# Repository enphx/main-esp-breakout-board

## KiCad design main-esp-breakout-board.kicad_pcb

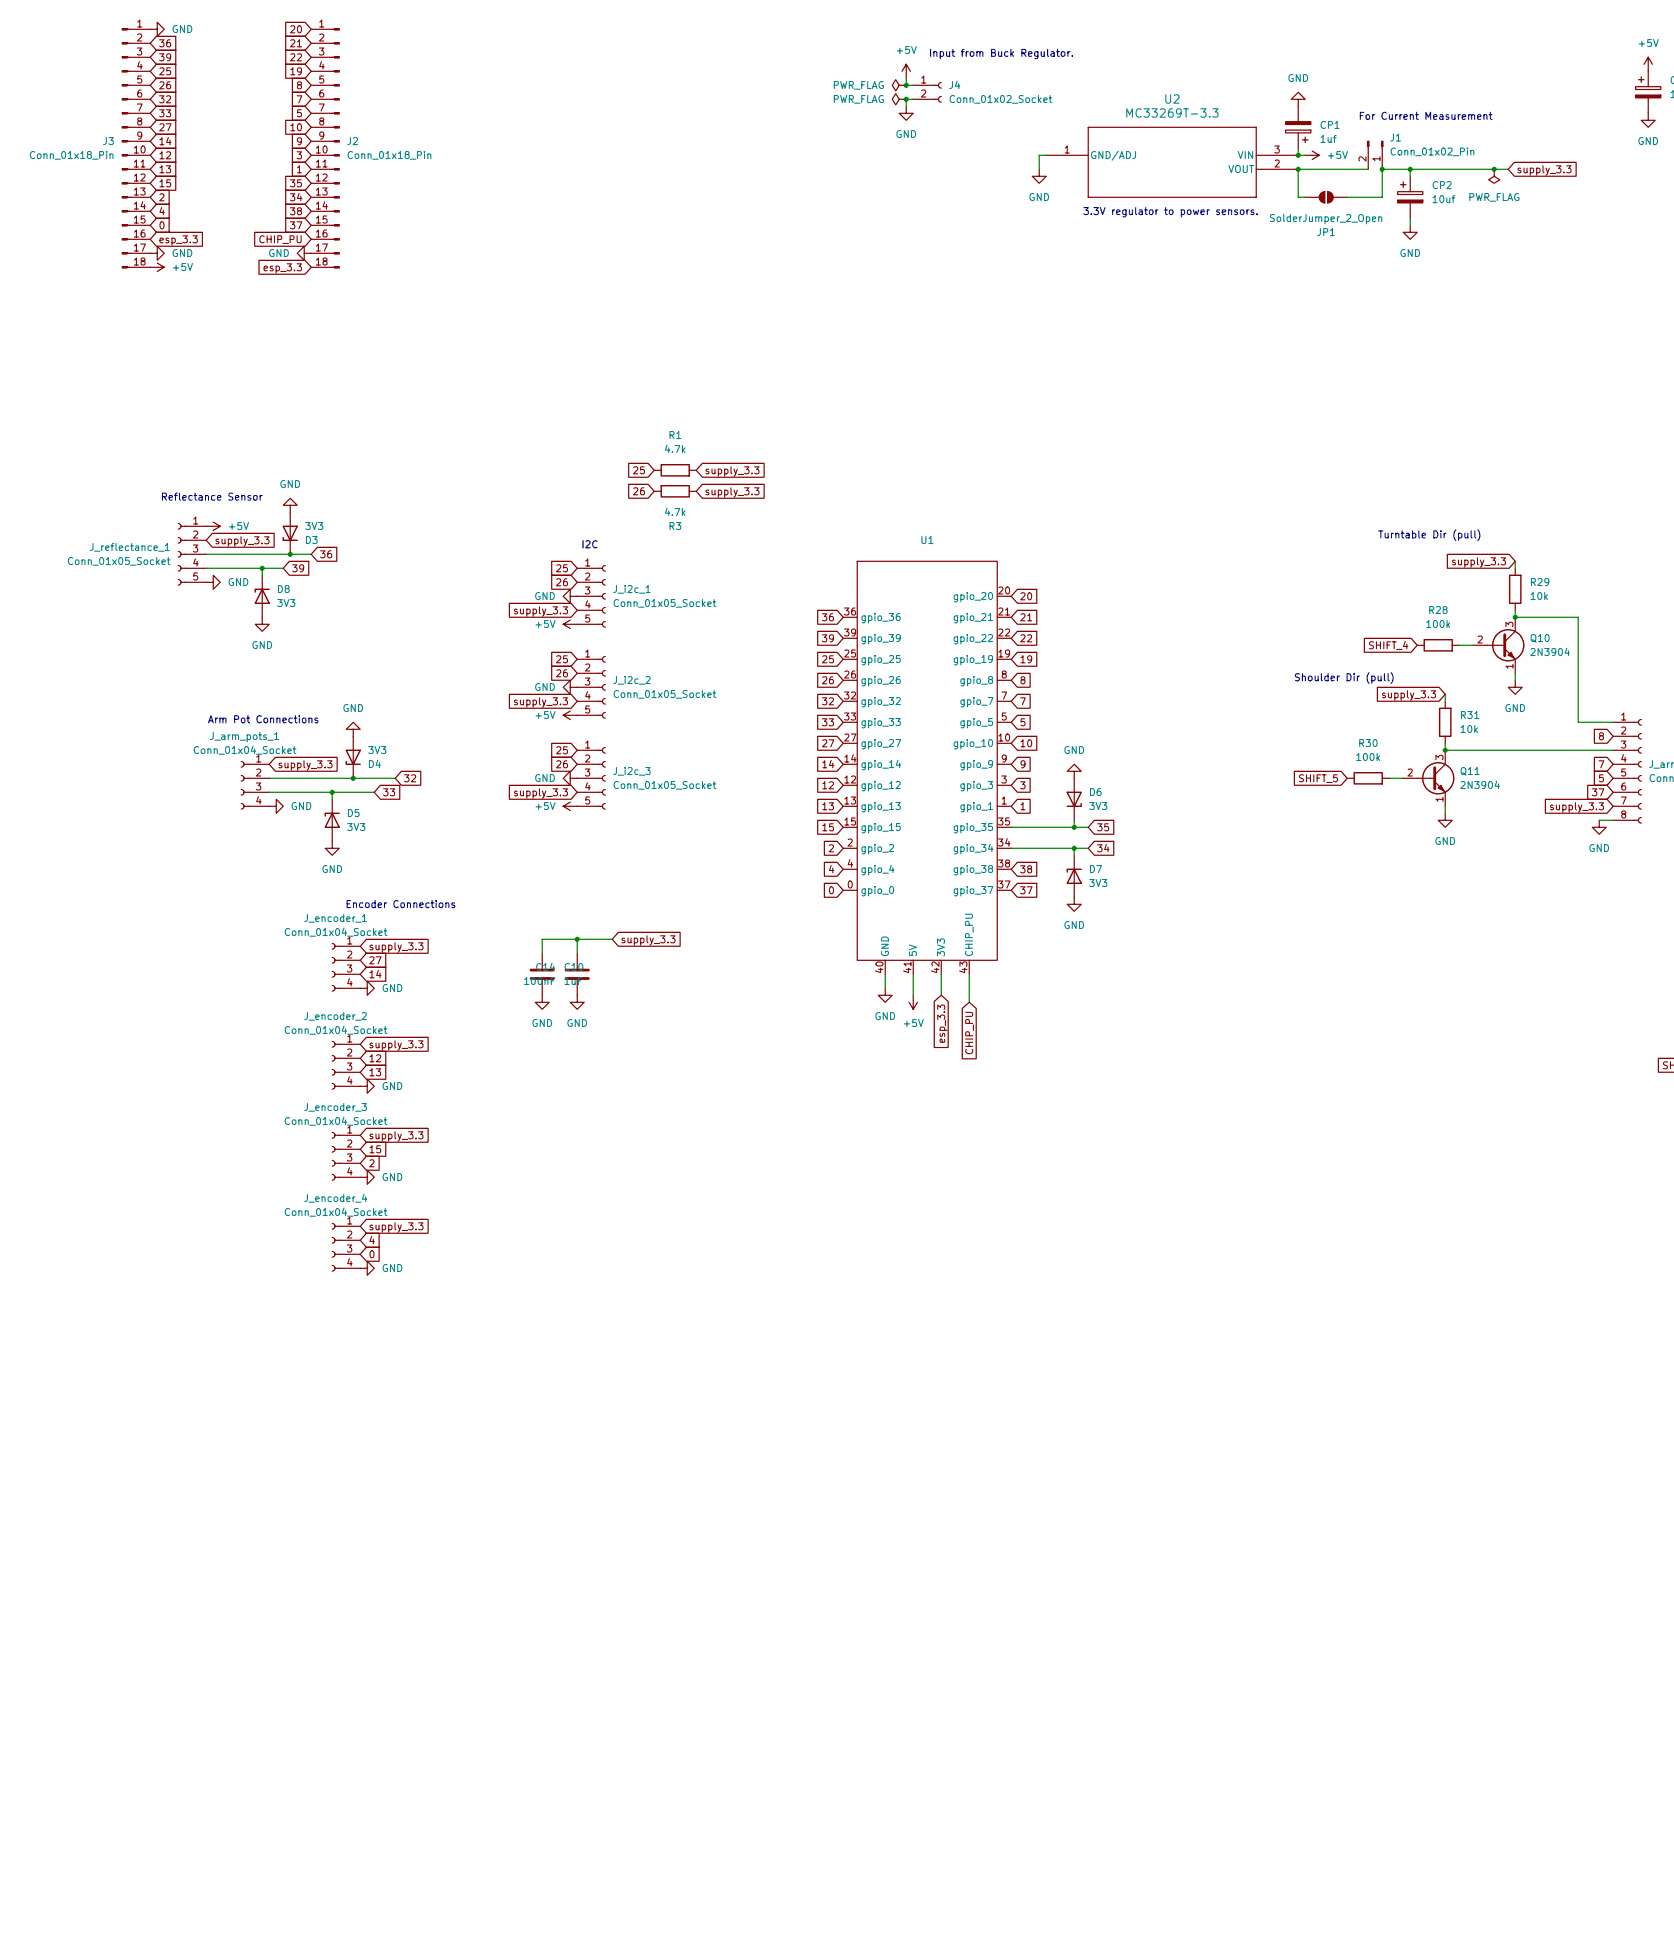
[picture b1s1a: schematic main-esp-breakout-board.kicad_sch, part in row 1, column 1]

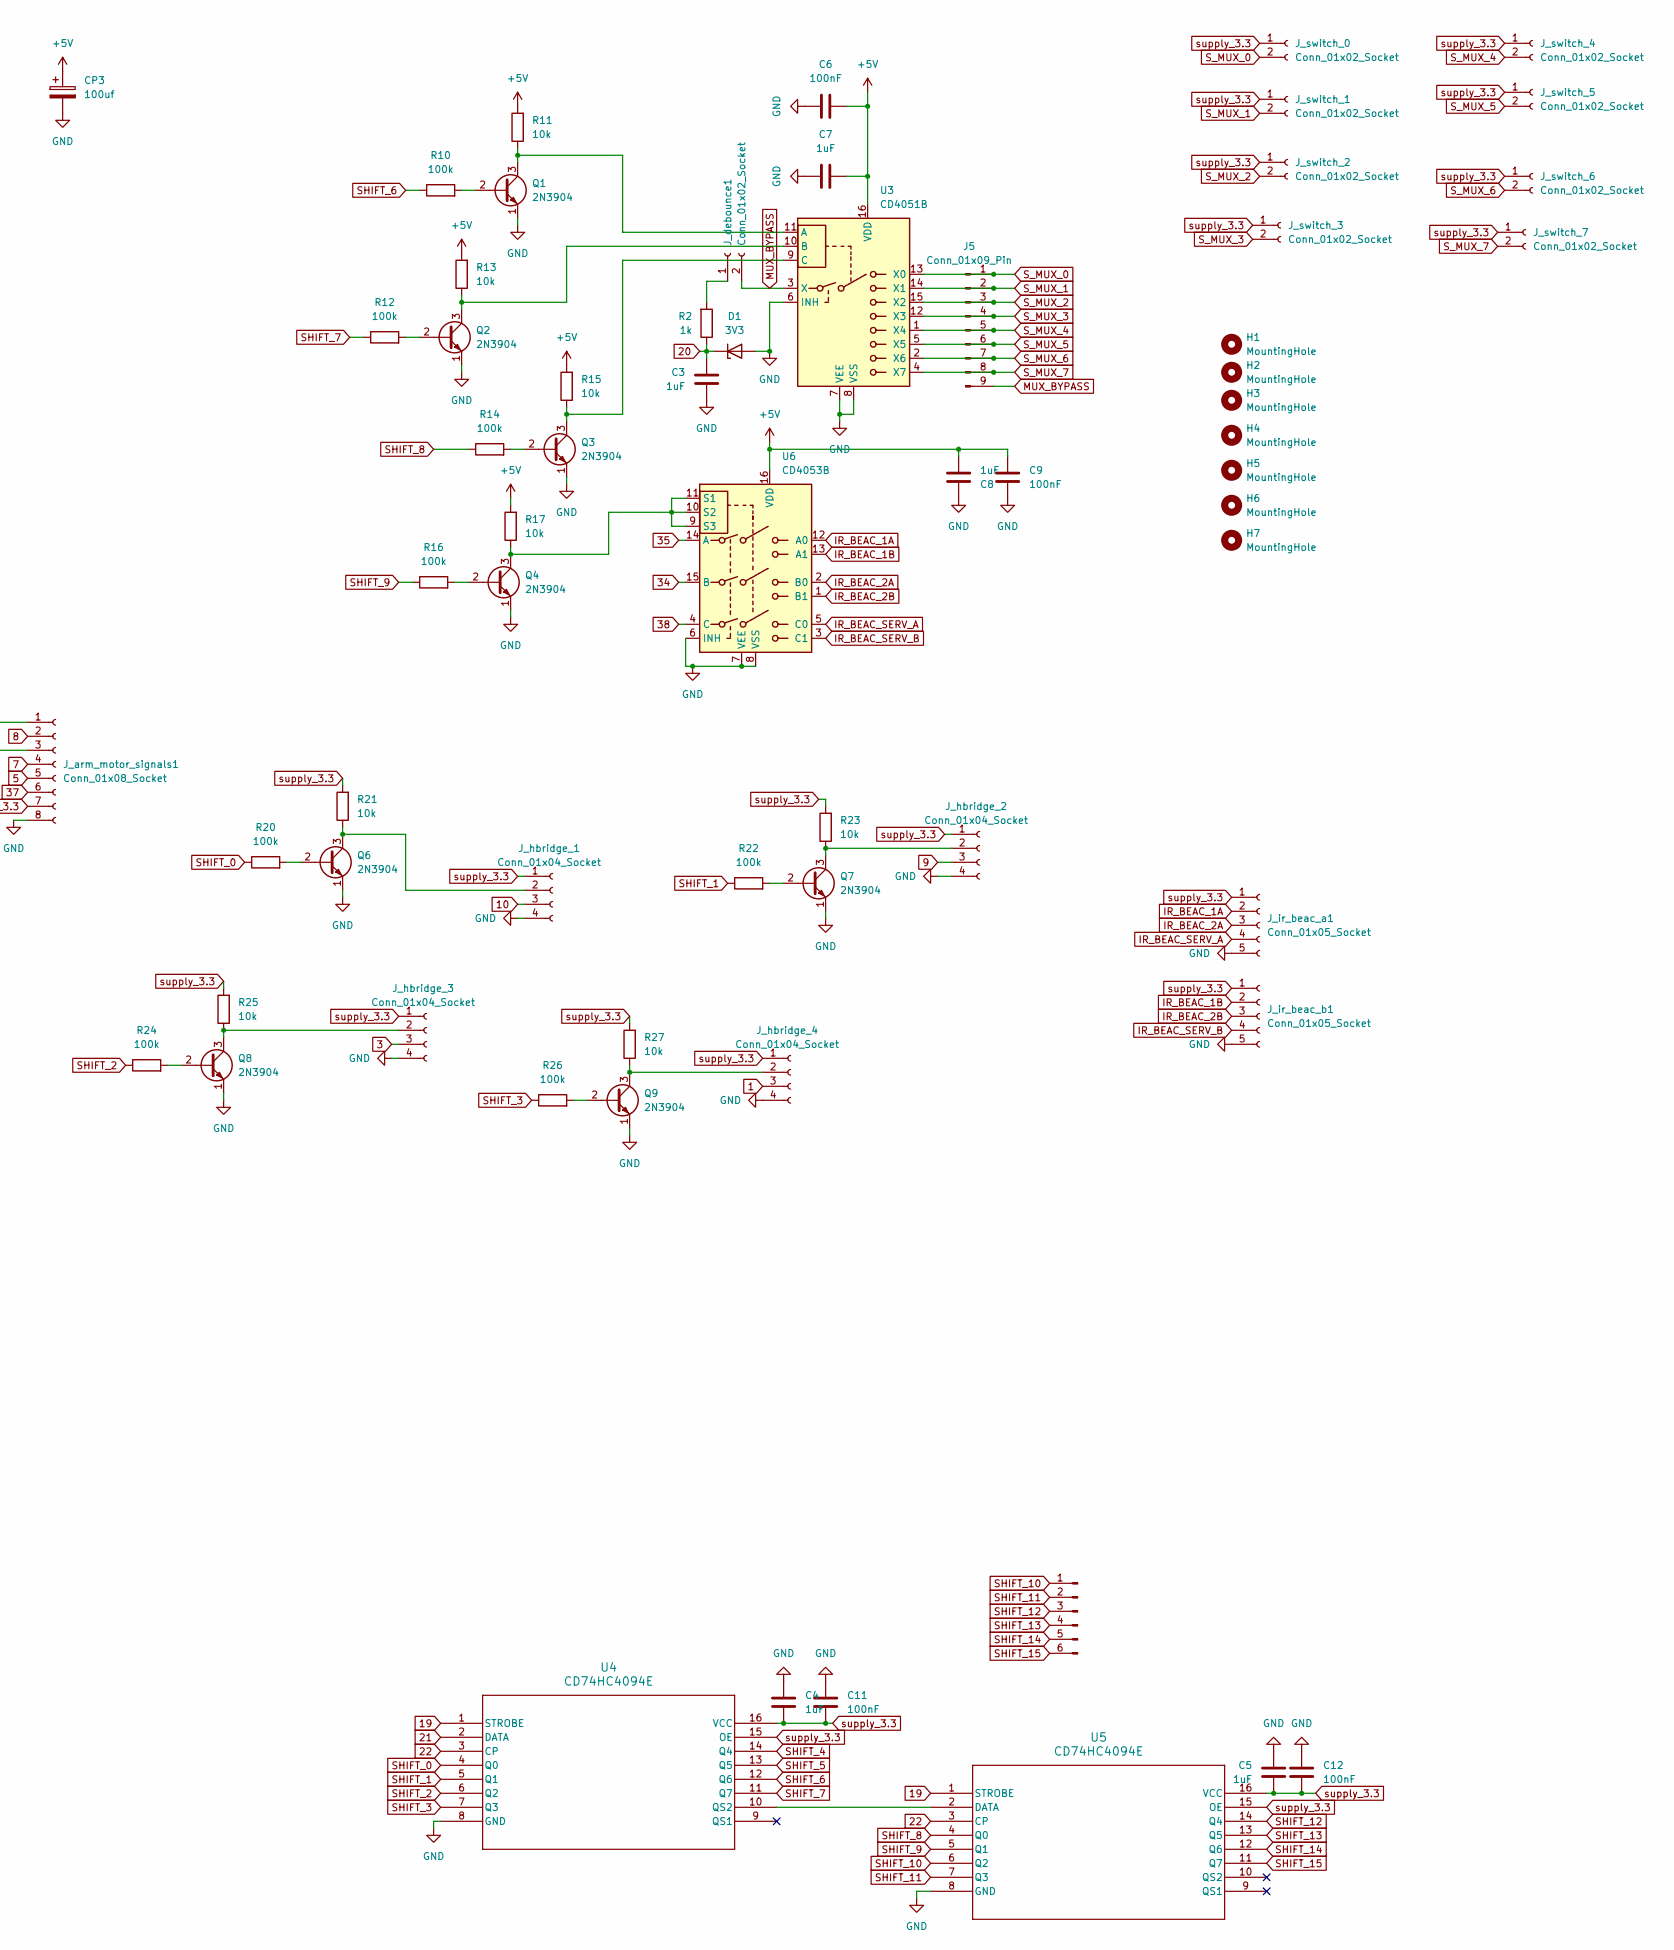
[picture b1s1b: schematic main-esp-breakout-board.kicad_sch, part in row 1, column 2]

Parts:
C3, C4, C5, C7, C8, C10: 1uF; Capacitor_With_Value_uF_small
C6, C9, C11, C12, C14: 100nF; Capacitor_With_Value_nF
CP1: 1uf; Capacitor_With_Value_uF_small
CP2: 10uf; Capacitor_With_Value_uF_small
CP3: 100uf; Capacitor_With_Value_uF_big
D1, D3, D4, D5, D6, D7, D8: 3V3; zener_diode
H1, H2, H3, H4, H5, H6, H7: MountingHole; MountingHole_3.2mm_M3
J1: Conn_01x02_Pin; PinHeader_1x02_P2.54mm_Vertical
J2, J3: Conn_01x18_Pin; PinHeader_1x18_P2.54mm_Vertical
J4: Conn_01x02_Socket; Power_Connector
J5: Conn_01x09_Pin; PinHeader_1x09_P2.54mm_Vertical
JP1: SolderJumper_2_Open; SolderJumper-2_P1.3mm_Open_RoundedPad1.0x1.5mm
J_arm_motor_signals1: Conn_01x08_Socket; JST_XH_B8B-XH-A_1x08_P2.50mm_Vertical
J_arm_pots_1: Conn_01x04_Socket; JST_XH_B4B-XH-A_1x04_P2.50mm_Vertical
J_debounce1: Conn_01x02_Socket; JST_XH_B2B-XH-A_1x02_P2.50mm_Vertical
J_encoder_1, J_encoder_2, J_encoder_3, J_encoder_4: Conn_01x04_Socket; JST_XH_B4B-XH-A_1x04_P2.50mm_Vertical
J_hbridge_1, J_hbridge_2, J_hbridge_3, J_hbridge_4: Conn_01x04_Socket; JST_XH_B4B-XH-A_1x04_P2.50mm_Vertical
J_i2c_1, J_i2c_2, J_i2c_3: Conn_01x05_Socket; JST_XH_B5B-XH-A_1x05_P2.50mm_Vertical
J_ir_beac_a1: Conn_01x05_Socket; JST_XH_B5B-XH-A_1x05_P2.50mm_Vertical
J_ir_beac_b1: Conn_01x05_Socket; JST_XH_B5B-XH-A_1x05_P2.50mm_Vertical
J_reflectance_1: Conn_01x05_Socket; JST_XH_B5B-XH-A_1x05_P2.50mm_Vertical
J_shift_register_extra1: Conn_01x06_Pin; PinSocket_1x06_P2.54mm_Vertical
J_switch_0, J_switch_1, J_switch_2, J_switch_3, J_switch_4, J_switch_5, J_switch_6, J_switch_7: Conn_01x02_Socket; JST_XH_B2B-XH-A_1x02_P2.50mm_Vertical
Q1, Q2, Q3, Q4, Q6, Q7, Q8, Q9, Q10, Q11: 2N3904; TO-92_Inline
R1, R3: 4.7k; Resistor_With_Value
R2: 1k; Resistor_With_Value
R10, R12, R14, R16, R20, R22, R24, R26, R28, R30: 100k; Resistor_With_Value
R11, R13, R15, R17, R21, R23, R25, R27, R29, R31: 10k; Resistor_With_Value
U1: ESP32_Pico_Devkit
U2: MC33269T-3.3; TO220-3_ONS
U3: CD4051B; N16
U4, U5: CD74HC4094E; N16
U6: CD4053B; N16

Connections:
0: J3.15, J_encoder_4.3, U1.0 (gpio_0)
1: J2.11, J_hbridge_4.3, U1.1 (gpio_1)
2: J3.13, J_encoder_3.3, U1.2 (gpio_2)
3: J2.10, J_hbridge_3.3, U1.3 (gpio_3)
4: J3.14, J_encoder_4.2, U1.4 (gpio_4)
5: J2.7, J_arm_motor_signals1.5, U1.5 (gpio_5)
7: J2.6, J_arm_motor_signals1.4, U1.7 (gpio_7)
8: J2.5, J_arm_motor_signals1.2, U1.8 (gpio_8)
9: J2.9, J_hbridge_2.3, U1.9 (gpio_9)
10: J2.8, J_hbridge_1.3, U1.10 (gpio_10)
12: J3.10, J_encoder_2.2, U1.12 (gpio_12)
13: J3.11, J_encoder_2.3, U1.13 (gpio_13)
14: J3.9, J_encoder_1.3, U1.14 (gpio_14)
15: J3.12, J_encoder_3.2, U1.15 (gpio_15)
19: J2.4, U1.19 (gpio_19), U4.1 (STROBE), U5.1 (STROBE)
20: C3.1, D1.1 (K), J2.1, R2.1, U1.20 (gpio_20)
21: J2.2, U1.21 (gpio_21), U4.2 (DATA)
22: J2.3, U1.22 (gpio_22), U4.3 (CP), U5.3 (CP)
25: J3.4, J_i2c_1.1, J_i2c_2.1, J_i2c_3.1, R1.1, U1.25 (gpio_25)
26: J3.5, J_i2c_1.2, J_i2c_2.2, J_i2c_3.2, R3.2, U1.26 (gpio_26)
27: J3.8, J_encoder_1.2, U1.27 (gpio_27)
32: D4.1 (K), J3.6, J_arm_pots_1.2, U1.32 (gpio_32)
33: D5.1 (K), J3.7, J_arm_pots_1.3, U1.33 (gpio_33)
34: D7.1 (K), J2.13, U1.34 (gpio_34), U6.15 (B)
35: D6.1 (K), J2.12, U1.35 (gpio_35), U6.14 (A)
36: D3.1 (K), J3.2, J_reflectance_1.3, U1.36 (gpio_36)
37: J2.15, J_arm_motor_signals1.6, U1.37 (gpio_37)
38: J2.14, U1.38 (gpio_38), U6.4 (C)
39: D8.1 (K), J3.3, J_reflectance_1.4, U1.39 (gpio_39)
+5V: C6.2, C7.1, C8.1, C9.2, CP1.1, CP3.1, J3.18, J4.1, J_i2c_1.5, J_i2c_2.5, J_i2c_3.5, J_reflectance_1.1, R11.2, R13.2, R15.2, R17.2, U1.41 (5V), U2.3 (VIN), U3.16 (VDD), U6.16 (VDD)
CHIP_PU: J2.16, U1.43 (CHIP_PU)
GND: C3.2, C4.2, C5.2, C6.1, C7.2, C8.2, C9.1, C10.2, C11.1, C12.1, C14.1, CP1.2, CP2.2, CP3.2, D1.2 (A), D3.2 (A), D4.2 (A), D5.2 (A), D6.2 (A), D7.2 (A), D8.2 (A), J2.17, J3.1, J3.17, J4.2, J_arm_motor_signals1.8, J_arm_pots_1.4, J_encoder_1.4, J_encoder_2.4, J_encoder_3.4, J_encoder_4.4, J_hbridge_1.4, J_hbridge_2.4, J_hbridge_3.4, J_hbridge_4.4, J_i2c_1.3, J_i2c_2.3, J_i2c_3.3, J_ir_beac_a1.5, J_ir_beac_b1.5, J_reflectance_1.5, Q1.1 (E), Q2.1 (E), Q3.1 (E), Q4.1 (E), Q6.1 (E), Q7.1 (E), Q8.1 (E), Q9.1 (E), Q10.1 (E), Q11.1 (E), U1.40 (GND), U2.1 (GND/ADJ), U3.6 (INH), U3.7 (VEE), U3.8 (VSS), U4.8 (GND), U5.8 (GND), U6.6 (INH), U6.7 (VEE), U6.8 (VSS)
IR_BEAC_1A: J_ir_beac_a1.2, U6.12 (A0)
IR_BEAC_1B: J_ir_beac_b1.2, U6.13 (A1)
IR_BEAC_2A: J_ir_beac_a1.3, U6.2 (B0)
IR_BEAC_2B: J_ir_beac_b1.3, U6.1 (B1)
IR_BEAC_SERV_A: J_ir_beac_a1.4, U6.5 (C0)
IR_BEAC_SERV_B: J_ir_beac_b1.4, U6.3 (C1)
MUX_BYPASS: J5.9, J_debounce1.2, U3.3 (X)
unnamed: J1.2, JP1.1 (A), U2.2 (VOUT)
unnamed: J_arm_motor_signals1.1, Q10.3 (C), R29.1
unnamed: J_arm_motor_signals1.3, Q11.3 (C), R31.1
unnamed: J_debounce1.1, R2.2
unnamed: J_hbridge_1.2, Q6.3 (C), R21.1
unnamed: J_hbridge_2.2, Q7.3 (C), R23.1
unnamed: J_hbridge_3.2, Q8.3 (C), R25.1
unnamed: J_hbridge_4.2, Q9.3 (C), R27.1
unnamed: Q1.2 (B), R10.2
unnamed: Q1.3 (C), R11.1, U3.11 (A)
unnamed: Q2.2 (B), R12.2
unnamed: Q2.3 (C), R13.1, U3.10 (B)
unnamed: Q3.2 (B), R14.2
unnamed: Q3.3 (C), R15.1, U3.9 (C)
unnamed: Q4.2 (B), R16.2
unnamed: Q4.3 (C), R17.1, U6.9 (S3), U6.10 (S2), U6.11 (S1)
unnamed: Q6.2 (B), R20.2
unnamed: Q7.2 (B), R22.2
unnamed: Q8.2 (B), R24.2
unnamed: Q9.2 (B), R26.2
unnamed: Q10.2 (B), R28.2
unnamed: Q11.2 (B), R30.2
unnamed: U4.10 (QS2), U5.2 (DATA)
SHIFT_0: R20.1, U4.4 (Q0)
SHIFT_1: R22.1, U4.5 (Q1)
SHIFT_2: R24.1, U4.6 (Q2)
SHIFT_3: R26.1, U4.7 (Q3)
SHIFT_4: R28.1, U4.14 (Q4)
SHIFT_5: R30.1, U4.13 (Q5)
SHIFT_6: R10.1, U4.12 (Q6)
SHIFT_7: R12.1, U4.11 (Q7)
SHIFT_8: R14.1, U5.4 (Q0)
SHIFT_9: R16.1, U5.5 (Q1)
SHIFT_10: J_shift_register_extra1.1, U5.6 (Q2)
SHIFT_11: J_shift_register_extra1.2, U5.7 (Q3)
SHIFT_12: J_shift_register_extra1.3, U5.14 (Q4)
SHIFT_13: J_shift_register_extra1.4, U5.13 (Q5)
SHIFT_14: J_shift_register_extra1.5, U5.12 (Q6)
SHIFT_15: J_shift_register_extra1.6, U5.11 (Q7)
S_MUX_0: J5.1, J_switch_0.2, U3.13 (X0)
S_MUX_1: J5.2, J_switch_1.2, U3.14 (X1)
S_MUX_2: J5.3, J_switch_2.2, U3.15 (X2)
S_MUX_3: J5.4, J_switch_3.2, U3.12 (X3)
S_MUX_4: J5.5, J_switch_4.2, U3.1 (X4)
S_MUX_5: J5.6, J_switch_5.2, U3.5 (X5)
S_MUX_6: J5.7, J_switch_6.2, U3.2 (X6)
S_MUX_7: J5.8, J_switch_7.2, U3.4 (X7)
esp_3.3: J2.18, J3.16, U1.42 (3V3)
supply_3.3: C4.1, C5.1, C10.1, C11.2, C12.2, C14.2, CP2.1, J1.1, JP1.2 (B), J_arm_motor_signals1.7, J_arm_pots_1.1, J_encoder_1.1, J_encoder_2.1, J_encoder_3.1, J_encoder_4.1, J_hbridge_1.1, J_hbridge_2.1, J_hbridge_3.1, J_hbridge_4.1, J_i2c_1.4, J_i2c_2.4, J_i2c_3.4, J_ir_beac_a1.1, J_ir_beac_b1.1, J_reflectance_1.2, J_switch_0.1, J_switch_1.1, J_switch_2.1, J_switch_3.1, J_switch_4.1, J_switch_5.1, J_switch_6.1, J_switch_7.1, R1.2, R3.1, R21.2, R23.2, R25.2, R27.2, R29.2, R31.2, U4.15 (OE), U4.16 (VCC), U5.15 (OE), U5.16 (VCC)

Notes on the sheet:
For Current Measurement
Encoder Connections
I2C
Shoulder Dir (pull)
Arm Pot Connections
Input from Buck Regulator.
Reflectance Sensor
3.3V regulator to power sensors.
Turntable Dir (pull)

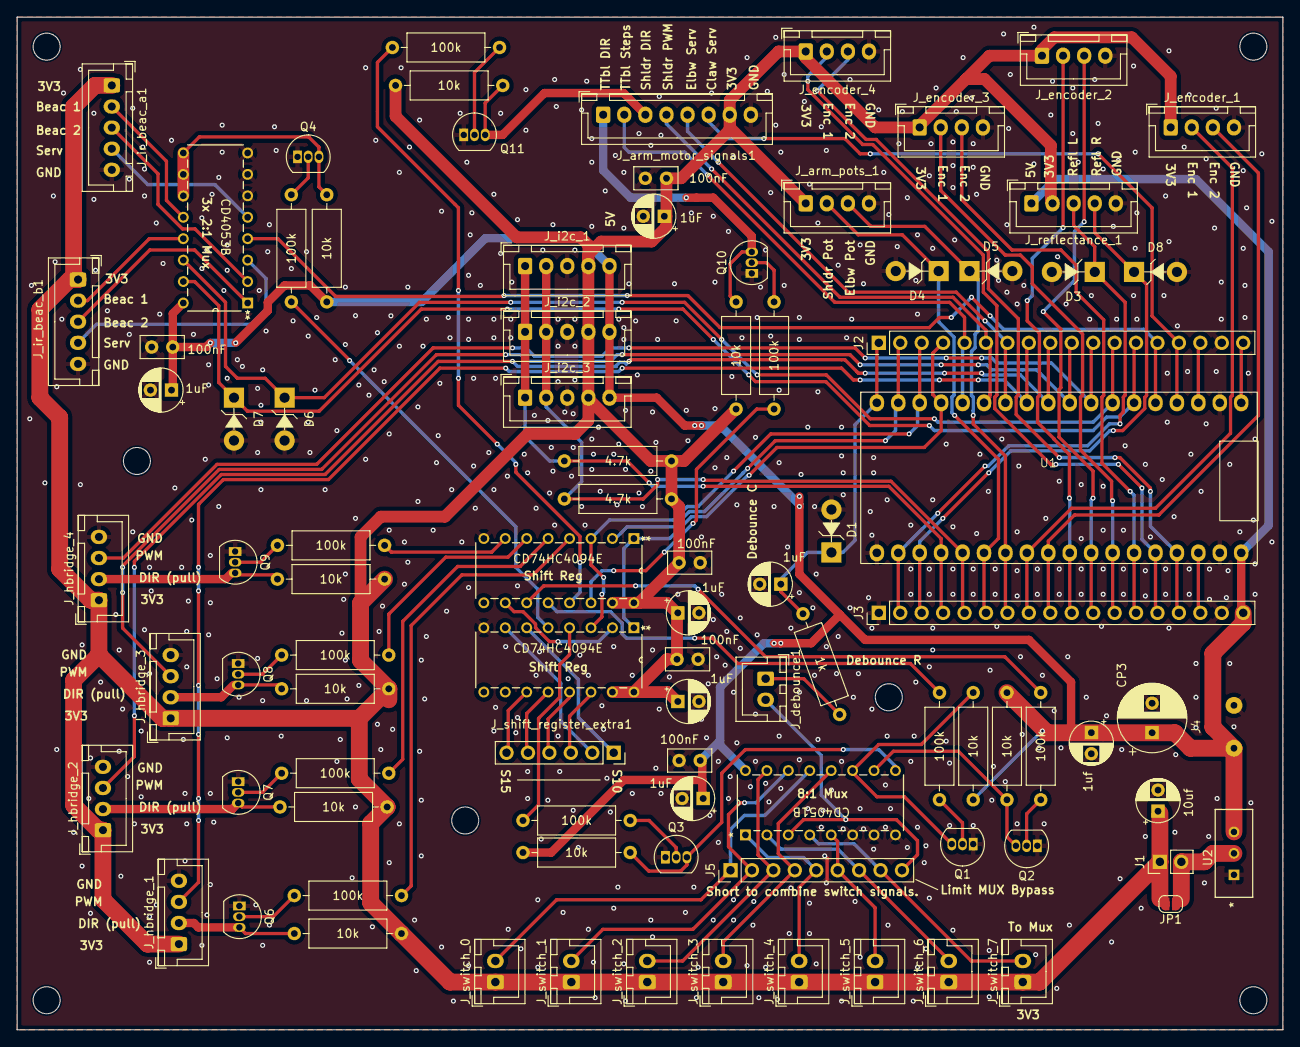
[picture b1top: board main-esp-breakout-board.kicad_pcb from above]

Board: 2 copper layers, 150.0 x 120.0 mm, 99 parts (0 on the bottom side), 88 nets.

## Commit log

2025-06-16 initialized repo.
2025-06-18 finished rudimentary schematic; still needs review and PCB layout...
2025-06-20 halfway thru layout...
2025-06-20 worked on layout some more...
2025-06-20 finished layout!
2025-06-22 finished PCB with silkscreen art! :D
